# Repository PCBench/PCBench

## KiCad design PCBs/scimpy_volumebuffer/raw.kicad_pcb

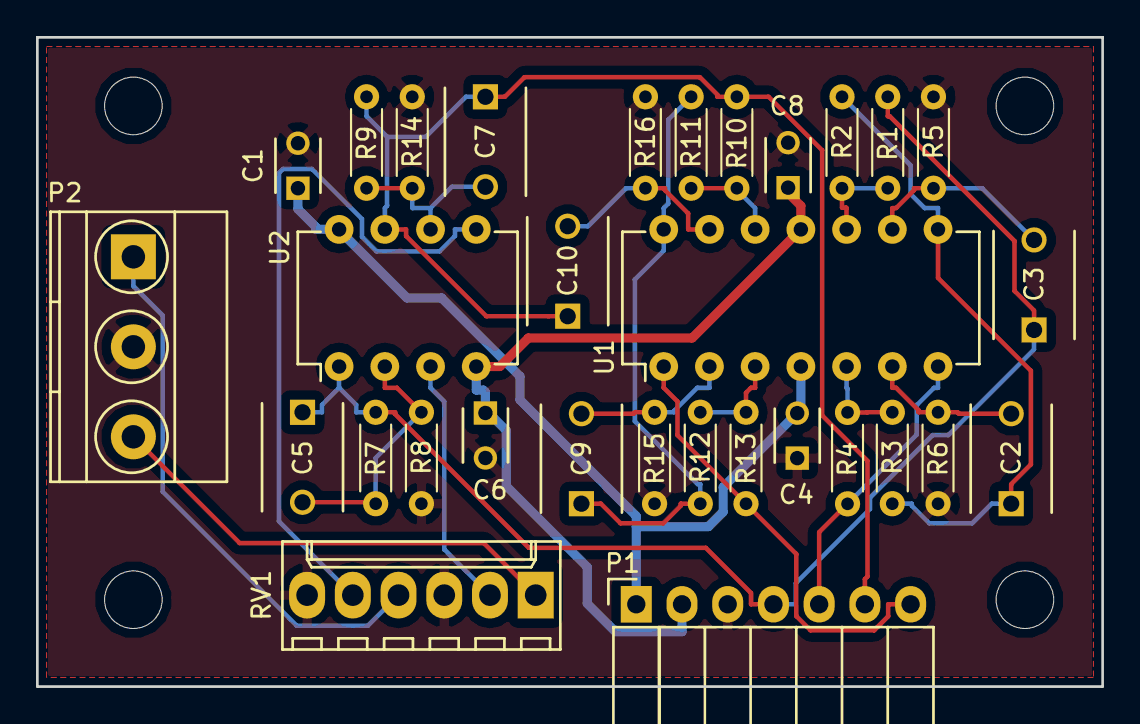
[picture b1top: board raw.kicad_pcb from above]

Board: 2 copper layers, 59.2 x 36.1 mm, 34 parts (0 on the bottom side), 23 nets.

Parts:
C1, C4, C6, C8: 100n; C_Disc_D3_P2.5
C2, C3, C5, C7, C9, C10: 100n; C_Disc_D6_P5
P1: CONN_01X07; Socket_Strip_Angled_1x07
P2: CONN_01X03; TerminalBlock_Pheonix_MKDS1.5-3pol
R1, R2, R3, R4, R10, R11, R12, R13: 2K2; R_Axial_DIN0204_L3.6mm_D1.6mm_P5.08mm_Horizontal
R5, R6, R15, R16: Rph; R_Axial_DIN0204_L3.6mm_D1.6mm_P5.08mm_Horizontal
R7, R9: Rbs1; R_Axial_DIN0204_L3.6mm_D1.6mm_P5.08mm_Horizontal
R8, R14: Rbs2; R_Axial_DIN0204_L3.6mm_D1.6mm_P5.08mm_Horizontal
RV1: DUAL_POT; Molex_KK-6410-06_06x2.54mm_Straight
U1: TL074; DIP-14_W7.62mm
U2: TL072; DIP-8_W7.62mm
mnt1, mnt2, mnt3: MountingHole_3.2mm_M3

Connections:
+15V: C1.1, C4.2, P1.1, U1.4, U2.8
-15V: C6.1, C8.1, P1.2, U1.11, U2.4
/left_bass: C3.1, C5.1, P1.4, R1.2, R7.2, U2.1
/left_in: P2.1, RV1.4
/left_tweet: P1.5, R4.1, U1.7
/right_bass: C7.1, C10.1, P1.6, R9.2, R10.2, U2.7
/right_in: P2.3, RV1.1
/right_tweet: P1.7, R13.1, U1.1
GND: C1.2, C4.1, C6.2, C8.2, P1.3, P2.2, R5.1, R6.1, R8.2, R14.1, R15.1, R16.1, RV1.3, RV1.6
unnamed: C2.1, R2.1, R3.2, U1.8
unnamed: C2.2, R6.2, U1.6
unnamed: C3.2, R5.2, U1.9
unnamed: C5.2, R7.1, R8.1, U2.2
unnamed: C7.2, R9.1, R14.2, U2.6
unnamed: C9.1, R11.1, R12.2, U1.14
unnamed: C9.2, R15.2, U1.2
unnamed: C10.2, R16.2, U1.13
unnamed: R1.1, R2.2, U1.10
unnamed: R3.1, R4.2, U1.5
unnamed: R10.1, R11.2, U1.12
unnamed: R12.1, R13.2, U1.3
unnamed: RV1.2, U2.3
unnamed: RV1.5, U2.5

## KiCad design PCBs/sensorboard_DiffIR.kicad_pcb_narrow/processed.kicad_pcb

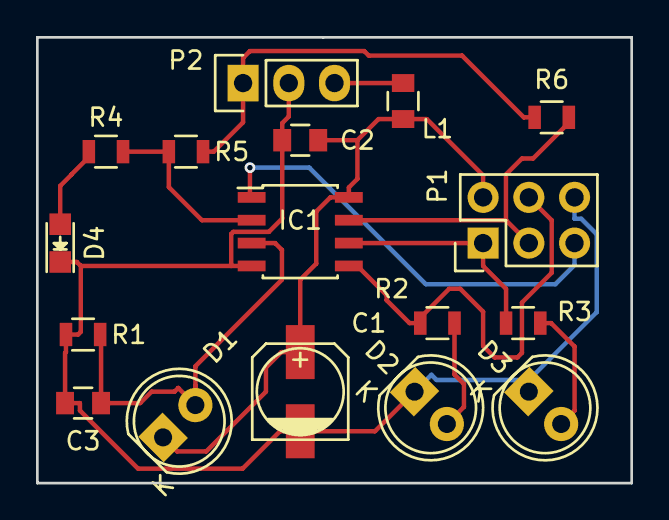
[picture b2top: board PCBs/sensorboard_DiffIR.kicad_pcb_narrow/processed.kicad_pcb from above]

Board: 2 copper layers, 33.0 x 24.8 mm, 17 parts (0 on the bottom side), 13 nets.

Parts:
C1: 22uF 25v; c_elec_5x5.7
C2: 100nF; C_0805
C3: 1nF; C_0805
D1: SFH3100F; LED-5MM
D2: IR1; LED-5MM
D3: IR2; LED-5MM
D4: PWR; LED_0805
IC1: ATTINY25-SS; SOIC-8_3.9x4.9mm_Pitch1.27mm
L1: 1uH; C_0805
P1: AVR_ISP; Pin_Header_Straight_2x03
P2: OUT; Pin_Header_Straight_1x03
R1: 6k8; R_0805
R2: 866R; R_0805
R3: 1k; R_0805
R4: 330R; R_0805
R5: 3k; R_0805
R6: 3k3; R_0805

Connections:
GND: C1.2, C2.2, C3.2, D2.1, D3.1, D4.1, IC1.4, P1.6, P2.2, R1.2
unnamed: C1.1, C2.1, D1.1, IC1.8, L1.1, P1.2
unnamed: D2.2, R2.2
unnamed: D3.2, R3.2
unnamed: D4.2, R4.2
unnamed: IC1.1, P1.5
unnamed: IC1.2, R4.1, R5.2
unnamed: IC1.5, P1.4, R2.1
unnamed: IC1.6, P1.1, R3.1
unnamed: IC1.7, P1.3, R6.2
unnamed: L1.2, P2.3
unnamed: P2.1, R5.1, R6.1
VCC: C3.1, D1.2, IC1.3, R1.1

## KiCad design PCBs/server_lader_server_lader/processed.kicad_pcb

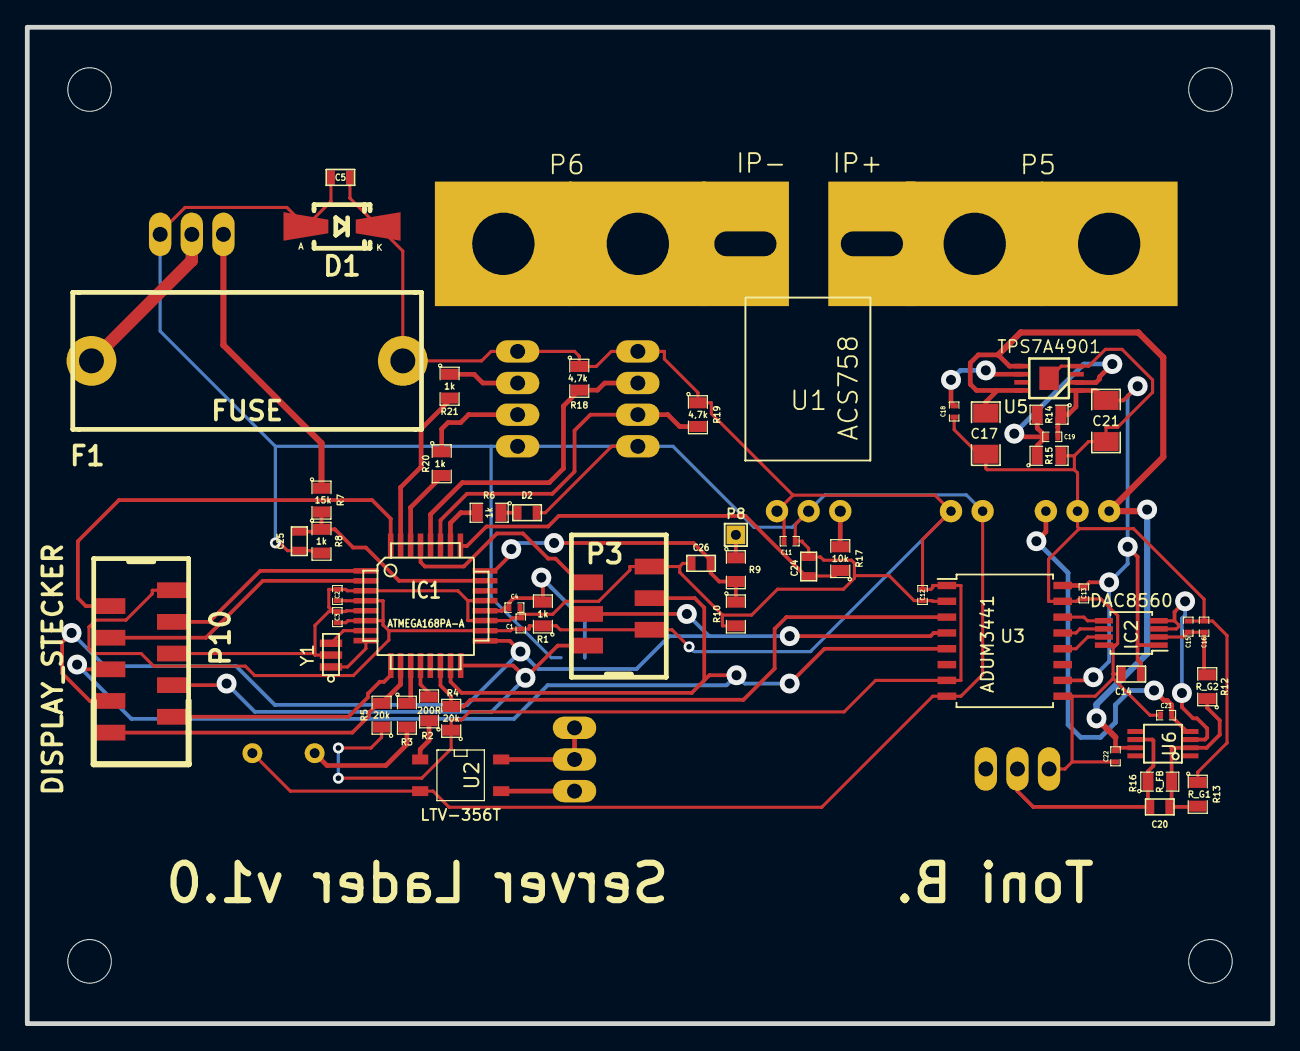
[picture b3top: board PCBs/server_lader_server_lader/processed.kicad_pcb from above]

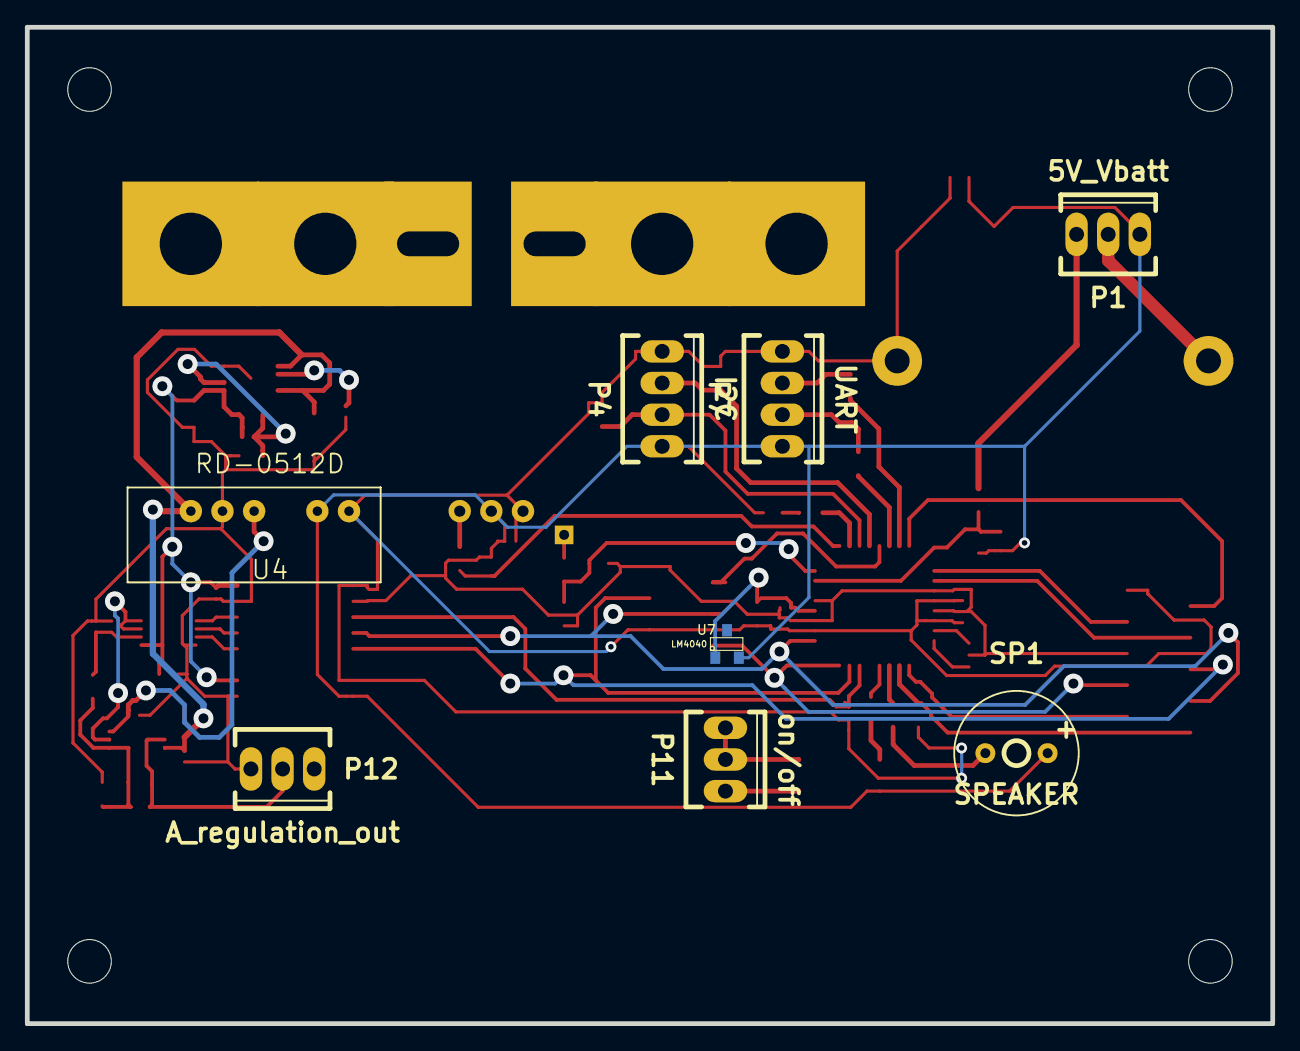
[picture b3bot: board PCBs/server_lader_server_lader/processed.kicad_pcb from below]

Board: 2 copper layers, 100.0 x 80.0 mm, 66 parts (8 on the bottom side), 51 nets.

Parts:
C1, C2, C3, C4, C11, C12, C13, C15, C16, C22, C23: 100nF; SMD-0402
C5, C14, C24: 1uF; SMD-0603
C17, C21: 10uF; SMD-1206
C18, C19: 10nF; SMD-0402
C20: C_comp; SMD-0603
C25: 100nF; SMD-0603
C26: C; SMD-0603
D1: ZENER 5,6V; Diode-Universal-SMA-SMB_Handsoldering
D2: LED; SMD-0603
F1: FUSE; fuse_holder_Schurther
IC1: ATMEGA168PA-A; TQFP-32
IC2: DAC8560; MSOP-8_3x3mm_Pitch0.65mm
Outl: EuroBoard_halb_Type-I_100mmX80mm_holes
P1: 5V_Vbatt; Socket_MOLEX-KK-RM2-54mm_Lock_3pin_straight
P3: CONN_02X03; micro_match3x2
P4: I2C; Socket_MOLEX-KK-RM2-54mm_Lock_4pin_straight
P5: IP+; power_terminal
P6: IP-; power_terminal
P7: UART; Socket_MOLEX-KK-RM2-54mm_Lock_4pin_straight
P8: CONN_01X01; SIL-1
P10: DISPLAY_STECKER; micro_match5x2
P11: on/off; Socket_MOLEX-KK-RM2-54mm_Lock_3pin_straight
P12: A_regulation_out; Socket_MOLEX-KK-RM2-54mm_Lock_3pin_straight
R1, R6, R8, R20, R21: 1k; SMD-0805
R2: 200R; SMD-0805
R3, R9, R10: R; SMD-0805
R4, R5: 20k; SMD-0805
R7: 15k; SMD-0805
R12: R_G2; SMD-0805
R13: R_G1; SMD-0805
R14: 33k; SMD-0805
R15, R17: 10k; SMD-0805
R16: R_FB; SMD-0805
R18, R19: 4,7k; SMD-0805
SP1: SPEAKER; Buzzer_AI-1027-TWT-5V-R
U1: ACS758; ACS758_PFF
U2: LTV-356T; SO-4
U3: ADUM3441; SOIC-16_7.5x10.3mm_Pitch1.27mm
U4: RD-0512D; RD-xx12D
U5: TPS7A4901; MSOP-8_power_pad
U6: OPA827; SSOP-8
U7: LM4040; SOT-23
Y1: RESONATEUR; CerOsc_3,2x1,3

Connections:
+5VA: C13.1, C14.1, C19.1, C21.1, IC2.1, R14.1, U3.10, U3.16, U5.1
+12V: C17.1, C22.1, U4.6, U5.5, U5.8, U6.7
-12V: C23.2, U4.4, U6.4
/A: IC1.32, P10.2
/B: IC1.1, P10.3
/CSB: IC1.10, P10.10, R5.2
/MISO: IC1.16, P3.1, P10.7
/MOSI: IC1.15, P3.4, P10.6, U3.5
/RS: IC1.9, P10.9
/RST: IC1.29, P3.5
/S: IC1.2, P10.4
/SCK: IC1.17, P3.3, P10.8, U3.4
/SCL: IC1.28, P4.3, R18.2
/SDA: IC1.27, P4.2, R19.2
/SS_DAC: IC1.14, R4.2, U3.3
/U_Netzteil: C25.1, IC1.23, R7.2, R8.1
/U_Strom: C24.1, IC1.25, R17.1
/U_reserve: C26.1, IC1.24, R9.2, R10.1
/V_current: C20.1, P12.2, R16.1, U6.6
/Vref: C15.1, C16.1, IC2.2, R12.2
/on: R2.1, U2.1
AGND: C13.2, C14.2, C15.2, C16.2, C17.2, C18.2, C21.2, C22.2, C23.1, IC2.8, P12.1, R13.1, R15.2, U3.9, U3.15, U4.5, U5.4, U5.9
GND: C1.2, C2.2, C3.2, C4.2, C5.2, C11.2, C12.2, C24.2, C25.2, C26.2, D1.1, D2.2, IC1.3, IC1.5, IC1.19, IC1.21, P1.1, P3.6, P4.1, P7.1, P10.5, R8.2, R10.2, SP1.2, U1.2, U2.2, U3.2, U3.8, U4.2, U7.2, Y1.2
unnamed: C4.1, IC1.20, R1.2, U7.1
unnamed: C18.1, U5.6
unnamed: C19.2, R14.2, R15.1, U5.2
unnamed: C20.2, R12.1, R13.2, R16.2, U6.2
unnamed: D2.1, R6.1
unnamed: F1.1, P1.2
unnamed: IC1.7, Y1.3
unnamed: IC1.8, Y1.1
unnamed: IC1.11, R3.1
unnamed: IC1.12, R2.2
unnamed: IC1.26, R6.2
unnamed: IC1.30, R20.2
unnamed: IC1.31, R21.2
unnamed: IC2.3, IC2.4, U6.3
unnamed: IC2.5, U3.14
unnamed: IC2.6, U3.13
unnamed: IC2.7, U3.12
unnamed: P1.3, R7.1
unnamed: P5.1, U1.4
unnamed: P6.1, U1.5
unnamed: P7.2, R20.1
unnamed: P7.3, R21.1
unnamed: P8.1, R9.1
unnamed: P11.1, U2.3
unnamed: P11.2, P11.3, U2.4
unnamed: R3.2, SP1.1
unnamed: R17.2, U1.3
VCC: C1.1, C2.1, C3.1, C5.1, C11.1, C12.1, D1.2, F1.2, IC1.4, IC1.6, IC1.18, P3.2, P4.4, P7.4, P10.1, R1.1, R4.1, R5.1, R18.1, R19.1, U1.1, U3.1, U3.7, U4.1

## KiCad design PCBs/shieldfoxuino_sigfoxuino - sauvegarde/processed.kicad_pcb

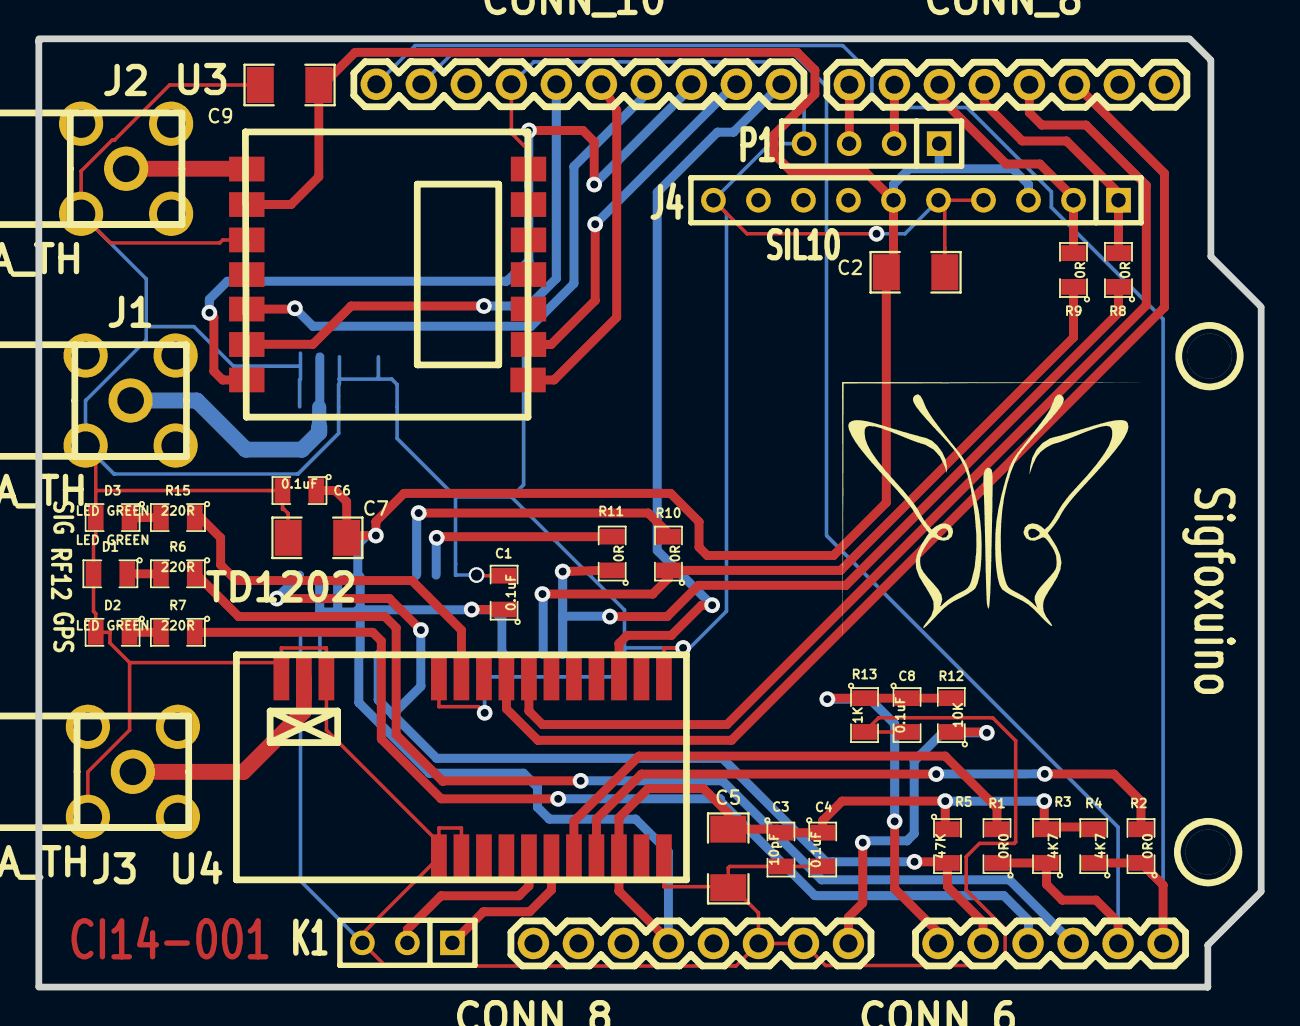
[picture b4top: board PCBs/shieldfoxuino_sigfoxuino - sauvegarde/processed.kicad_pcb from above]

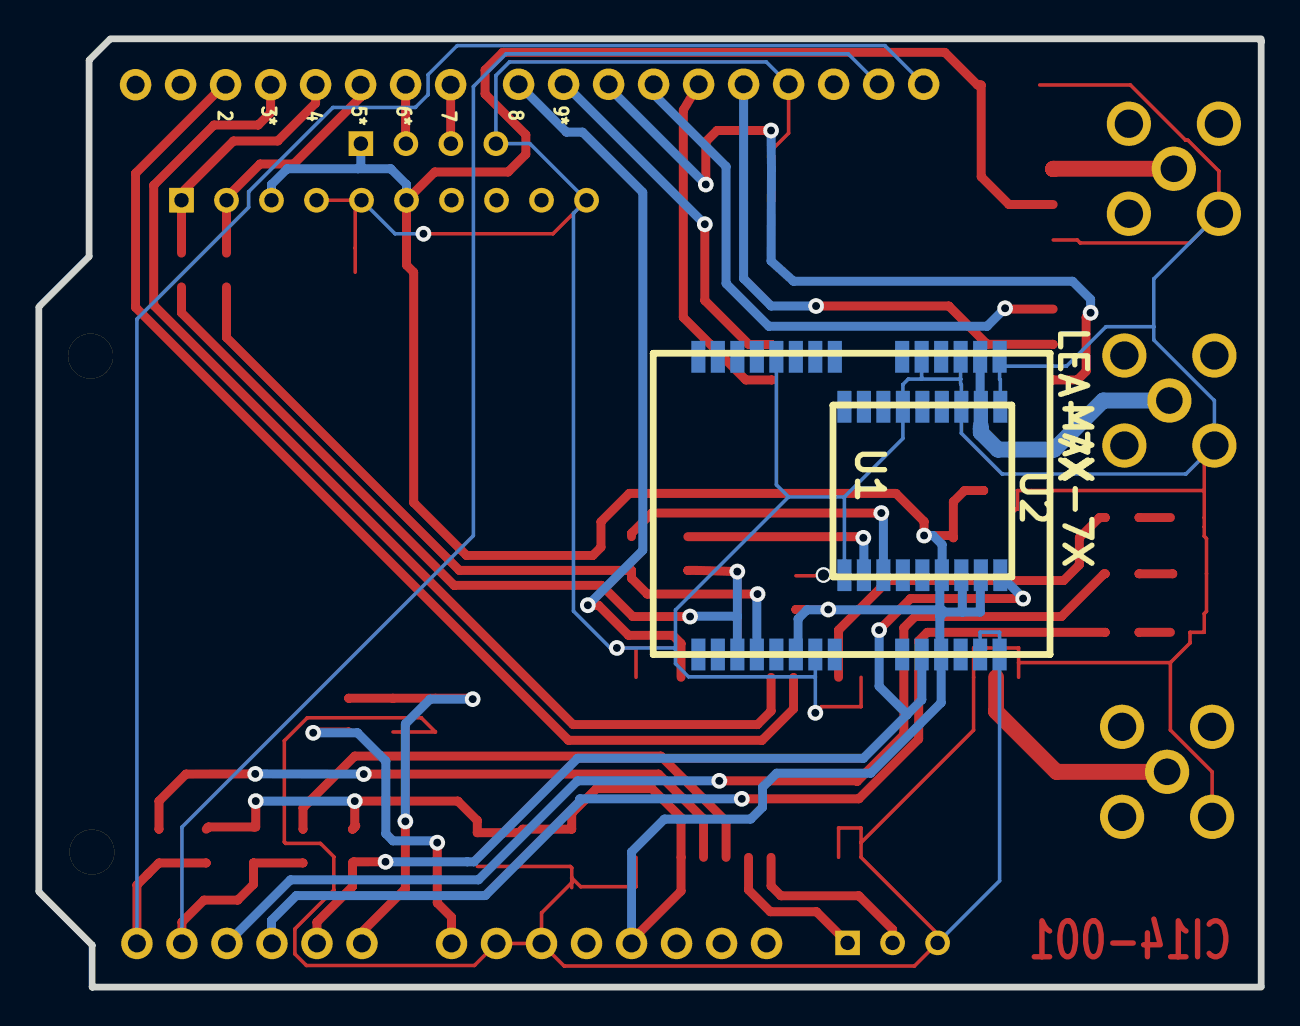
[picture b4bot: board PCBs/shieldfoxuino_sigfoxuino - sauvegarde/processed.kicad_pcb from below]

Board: 2 copper layers, 69.0 x 53.5 mm, 42 parts (2 on the bottom side), 36 nets.

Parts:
C1, C4, C6, C8: 0.1uF; SM0805
C2, C5, C7: 10uF/9V; SM1206
C3: 10pF; SM0805
C9: 1uF/9V; SM1206
CON6_1: CONN_6; Con6
CON8_1, CON8_2: CONN_8; Con8
CON10_1: CONN_10; Con10
D1, D2, D3: LED GREEN; SM0805
J1, J2, J3: SMA_TH; SMA-SMB_right_angle
J4: SIL10; SIL-10
K1: CONN_3; SIL-3
P1: CONN_4; SIL-4
R1, R2: 0R0; SM0805
R3, R4: 4K7; SM0805
R5: 47K; SM0805
R6, R7, R15: 220R; SM0805
R8, R9, R10, R11: 0R; SM0805
R12: 10K; SM0805
R13: 1K; SM0805
U1: LEA-7X; LEA-xx
U2: MAX-7X; MAX-xx
U3: RFM12
U4: TD1202
V4, V5: 1pin

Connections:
+3.3V: C1.1, C2.1, C3.1, C4.1, C5.1, C6.1, C7.1, C9.1, CON8_1.4, J4.3, J4.6, P1.1, R3.2, R4.2, R5.1, U1.6, U1.11, U2.6, U2.7, U2.8, U3.9, U4.9
/PB0: CON10_1.1, U4.14
/PB1: CON10_1.2, U3.2
/PB2: CON10_1.3, U3.14
/PB3: CON10_1.4, U3.12
/PB4: CON10_1.5, U3.1
/PB5: CON10_1.6, U3.13
/PC0: C8.1, CON6_1.1, R12.2, R13.1
/PC1: CON6_1.2, R5.2, U1.10, U2.9
/PC2: CON6_1.3, R7.1
/PC3: CON6_1.4, R6.1
/PD2: CON8_2.3, U4.19
/PD3: CON8_2.4, U4.18
/PD4: CON8_2.5, J4.1, R8.2
/PD5: CON8_2.6, J4.2, R9.2
/PD6: CON8_2.7, P1.2
/PD7: CON8_2.8, P1.3
/RF_GPS: J1.1, U1.16, U2.11
/RF_RF12: J2.1, U3.8
/RF_SIG: J3.1, U4.24
/RX_SFT: R8.1, R11.1, U1.3
/SCL: CON6_1.6, CON10_1.10, R2.1, R4.1
/SDA: CON6_1.5, CON10_1.9, R1.1, R3.1
/STATUS_SIG: R15.1, U4.21
/TX_SFT: R9.1, R10.1, U1.4
/VIN: CON8_1.8, R12.1
GND: C1.2, C2.2, C3.2, C4.2, C5.2, C6.2, C7.2, C8.2, C9.2, CON8_1.6, CON8_1.7, CON10_1.7, D1.2, D2.2, D3.2, J1.2, J2.2, J3.2, J4.4, J4.5, J4.10, K1.3, P1.4, R13.2, U1.7, U1.13, U1.14, U1.15, U1.17, U1.19, U1.24, U2.1, U2.10, U2.12, U2.15, U3.7, U3.10, U4.1, U4.2, U4.11, U4.12, U4.22, U4.23, U4.25
unnamed: R2.2, U4.8
unnamed: K1.2, U4.5
unnamed: K1.1, U4.6
unnamed: R11.2, U2.2
unnamed: R10.2, U2.3
unnamed: R1.2, U4.7
unnamed: D2.1, R7.2
unnamed: D1.1, R6.2
unnamed: D3.1, R15.2
